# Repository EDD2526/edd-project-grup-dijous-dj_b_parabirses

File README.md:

# Projecte DJ_B_PARABRISAS

>**Autors:Héctor Rodriguez y MariPaz Carreño
>**Versió: VFinal

----------

## Objectiu

>Crear un pcb para un limpia parabrisas, la cual tendrá control a través de un microcontrolador.
EL objetivo principal es  mantener  la luna del cristal limpia, para ello tenemos un sensor de lluvia que detectará la lluvia, un calefactor para que no se empañe, y bombas de agua que permitan en todo momento limpiar la luna.

## Diagrama de blocs

### Descripció/funcionalitat de cada bloc

  Tenemos el micro en el centro que funcionará como cerebro de todo.
  Como se puede observar uno de los sería la alimentación, consta de un conector que permite meter 12V, después pasa por un convertidor        
  DC-DC, para obtener 5V y por último un regulador para tener un voltaje de 3V.
  Por otro lado tenemos el bloque de potencia: consta de los drivers y motores de los limpiaparabrisas, de los circuitos relé tanto para 
  las bombas, como para el calefactor, y de finales de carrera que permitan volver a su estado inicial.   
  Por último un bloque de conexión/usuario: consta del BUS CAN, este permite la comunicación con otros módulos, el UART, transforma los 
  datos de forma que puedan ser leídos/enviados a un ordenador. También esta el sensor digital de lluvia que detecta cuando hay lluvia y 
  que el motor se ponga en marcha, y por último tendríamos la botonera: sirve para que el usuario acomode el modo del limpiaparabrisas o 
  encienda y apague el calefactor.       
  
-----------

## Requisits / Especificacions

* Alimentació: 12V d’entrada, regulada a 5V i 3.3V
* Microcontrolador: PIC24HJ64GP504
* Regulador buck: LM2596S-5 per obtenir 5V
* Regulador LDO: LM1117DT-3.3 per obtenir 3.3V
* Protecció d’entrada: díode TVS SM6T24A
* Díodes de protecció: D4, D5 i D6 per protegir contra pics inductius
* Comunicació CAN: transceptor TJA1049TK-3
* Comunicació RS232: MAX232
* Oscil·lador: cristall Y1 
* Condensadors de desacoblament: 100nF i 1uF
* Condensadors de filtratge: 680uF, 220uF, 100uF i 10uF
* Resistències: valors diversos per polarització, pull-up, pull-down i limitació de corrent
* Punts de test: TP1, TP2 i TP3

-----------

## Components

| Descripció | Ref | Package | Datasheet | Proveïdor | Preu | Unitats |
|---|---|---|---|---|---|---|
| Capacitor 100nF | C1,C2,C10,C16 | 0805 | ~ | Mouser | — | 4 |
| Capacitor 20pF | C3,C4 | 0805 | ~ | Mouser | — | 2 |
| Capacitor 1uF | C5,C6,C7,C8,C9 | 0805 | ~ | Mouser | — | 5 |
| Capacitor 680uF | C11 | 0805 | ~ | Mouser | — | 1 |
| Capacitor 220uF | C12 | 0805 | ~ | Mouser | — | 1 |
| Capacitor 10uF | C13,C14 | CP Radial D5.0mm P2.50mm | — | Mouser | — | 2 |
| Capacitor 100uF | C15 | CP Radial D5.0mm P2.50mm | — | Mouser | — | 1 |
| Capacitor 10pF | C17 | 0805 | ~ | Mouser | — | 1 |
| Capacitor 100pF | C19 | 0805 | ~ | Mouser | — | 1 |
| LED | D2 | LED 0805 | ~ | Mouser | — | 1 |
| Diodo TVS SM6T24A | D3 | SMB | https://www.st.com/resource/en/datasheet/sm6t.pdf | Mouser | — | 1 |
| Diodo genérico | D4,D5,D6 | 0201 | ~ | Mouser | — | 3 |
| Ferrita | FB1 | LairdTech 28C0236-0JW-10 | ~ | Mouser | — | 1 |
| Final de carrera SPDT | FINALCARRERA1,FINALCARRERA2 | XKB DM1-16UC-1 | ~ | Mouser | — | 2 |
| Conector 1x05 | J1 | PinHeader 1x05 2.54mm | ~ | Mouser | — | 1 |
| Conector DE9 | J2,J3 | DSUB-9 Horizontal | ~ | Mouser | — | 2 |
| Conector 1x02 | J4 | PinHeader 1x02 2.54mm | ~ | Mouser | — | 1 |
| Jumper 3 pines | JP1 | PinHeader 1x03 2.54mm | ~ | Mouser | — | 1 |
| Relé SPST-NO Fujitsu FTR-LYAA005x | K2,K3,K4 | Relay THT Vertical | https://www.fujitsu.com/sg/imagesgig5/ftr-ly.pdf | Mouser | — | 3 |
| Inductor 33uH | L1 | 0603 | ~ | Mouser | — | 1 |
| Motor DC / Bornera salida | M1,M2,M3,M5 | TerminalBlock 2P P5.00mm | ~ | Mouser | — | 4 |
| Transistor NPN MMBT3904 | Q2,Q3,Q4 | SOT-23 | https://www.onsemi.com/pdf/datasheet/pzt3904-d.pdf | Mouser | — | 3 |
| Resistencia 1k | R2,R3,R7,R8 | 0603 | ~ | Mouser | — | 4 |
| Resistencia 4.7k | R4,R13,R14 | 0603 | ~ | Mouser | — | 3 |
| Resistencia 121Ω | R5 | 0603 | ~ | Mouser | — | 1 |
| Resistencia 200Ω | R6 | 0603 | ~ | Mouser | — | 1 |
| Resistencia 10k | R9 | 0603 | ~ | Mouser | — | 1 |
| Resistencia 4.7k | R10 | 0603 | ~ | Mouser | — | 1 |
| Resistencia calefactor | R11 | 2512 | ~ | Mouser | — | 1 |
| Resistencia 60Ω | R12,R17 | 0201 | ~ | Mouser | — | 2 |
| Resistencia 10k | R15,R16 | 0603 | ~ | Mouser | — | 2 |
| Resistencia 7.6k | R18,R22,R23 | 0603 | ~ | Mouser | — | 3 |
| Resistencia 10k | R19,R20,R21 | 0201 | ~ | Mouser | — | 3 |
| Pulsador calefactor | SW1 | Alps SKRK SMD | ~ | Mouser | — | 1 |
| Pulsador bombas | SW2 | Alps SKRK SMD | ~ | Mouser | — | 1 |
| Pulsador | SW3 | Alps SKRK SMD | ~ | Mouser | — | 1 |
| Selector rotativo SP3T | SW5 | NKK NR01 THT | https://www.nkkswitches.com/pdf/NR01%20Rotaries.pdf | Mouser | — | 1 |
| Test point | TP1,TP2,TP3 | Keystone 5015 Micro Mini | ~ | Mouser | — | 3 |
| Regulador LDO 3.3V LM1117DT-3.3 | U1 | TO-252-3 | http://www.ti.com/lit/ds/symlink/lm1117.pdf | Mouser | — | 1 |
| Regulador buck 5V LM2596S-5 | U2 | TO-263-5 | http://www.ti.com/lit/ds/symlink/lm2596.pdf | Mouser | — | 1 |
| Driver motor DRV8871DDA | U3,U7 | HTSOP-8 PowerPAD | http://www.ti.com/lit/ds/symlink/drv8871.pdf | Mouser | — | 2 |
| Microcontrolador PIC24HJ64GP504 | U4 | QFN-44 7x7mm | — | Mouser | — | 1 |
| Sensor humedad/temperatura HDC2080 | U6 | Texas S-PWSON-N6 | http://www.ti.com/lit/ds/symlink/hdc2080.pdf | Mouser | — | 1 |
| Transceptor CAN TJA1049TK-3 | U8 | HVSON-8 | https://www.nxp.com/docs/en/data-sheet/TJA1049.pdf | Mouser | — | 1 |
| Transceptor RS232 MAX232 | U9 | SOIC-16 | http://www.ti.com/lit/ds/symlink/max232.pdf | Mouser | — | 1 |
| Cristal | Y1 | SMD EuroQuartz EQ161 2Pin | ~ | Mouser | — | 1 |

-----------

## Software

### Eines:

  * KiCad 9.0 o superior
  * 

### Configuraci&#243; :

  * 

### Funcionalitats:

  Gestionar el movimiento de las escobillas, el rociado del líquido limpiador mediante dos bombas y el calentamiento del sistema mediante un calefactor.
Cuando el usuario activa el mando, la PCB recibe la señal y enciende el motor del limpiaparabrisas en el modo seleccionado. También puede activar una de las dos bombas, por ejemplo una para el parabrisas delantero y otra para el cristal trasero, enviando líquido limpiador antes o durante el movimiento de las escobillas.
Además, la PCB controla el calefactor, que sirve para calentar el líquido o la zona del sistema de lavado, evitando congelación y mejorando el funcionamiento en bajas temperaturas.

-----------

## Historial de canvis

| Data | Autor     | Branch | Versi&#243; | Descripci&#243; |
| --- | --- | --- | --- | --- |
|  28/03/2023 | mlopez | Master | initial commit | Primera versi&#243; d'esquem&#224;tic i selecci&#243; de components |

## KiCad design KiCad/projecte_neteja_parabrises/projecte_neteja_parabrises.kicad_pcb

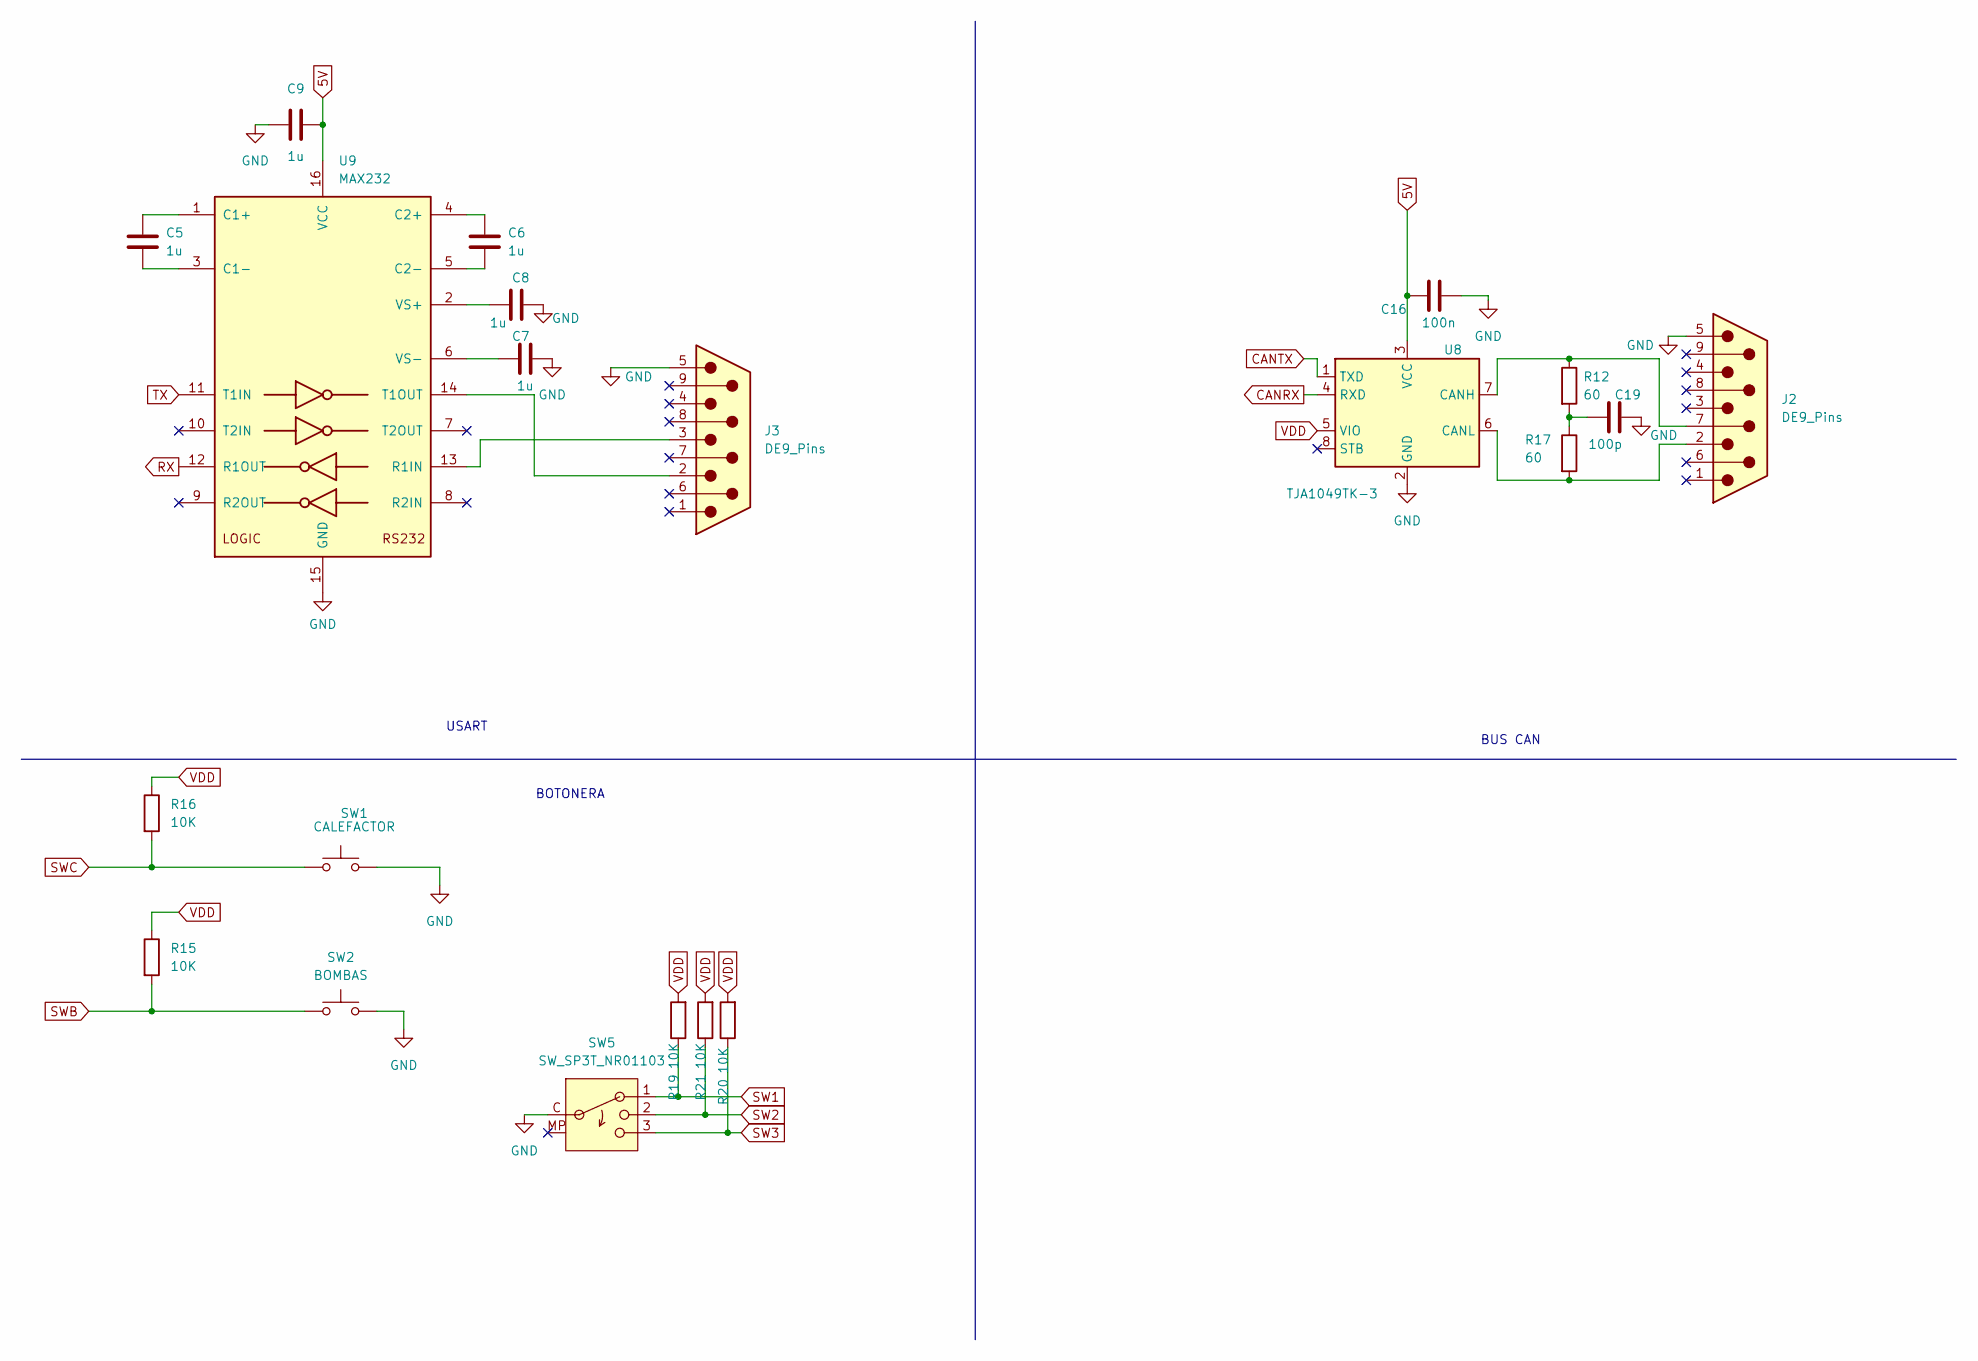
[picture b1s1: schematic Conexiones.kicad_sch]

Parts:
C5, C6, C7, C8, C9: 1u; C_0805_2012Metric
C16: 100n; C_0805_2012Metric
C19: 100p; C_0805_2012Metric
J2, J3: DE9_Pins; DSUB-9_Pins_Horizontal_P2.77x2.84mm_EdgePinOffset9.40mm
R12, R17: 60; R_0201_0603Metric_Pad0.64x0.40mm_HandSolder
R15, R16: 10K; R_0603_1608Metric_Pad0.98x0.95mm_HandSolder
R19, R20, R21: 10K; R_0201_0603Metric_Pad0.64x0.40mm_HandSolder
SW1: CALEFACTOR; SW_Push_SPST_NO_Alps_SKRK
SW2: BOMBAS; SW_Push_SPST_NO_Alps_SKRK
SW5: SW_SP3T_NR01103; SW_NKK_NR01
U8: TJA1049TK-3; HVSON-8-1EP_3x3mm_P0.65mm_EP1.6x2.4mm
U9: MAX232; JEITA_SOIC-16_3.9x9.9mm_P1.27mm

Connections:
5V: C9.2, C16.1, U8.3 (VCC), U9.16 (VCC); also elsewhere on the board
CANRX: U8.4 (RXD); also elsewhere on the board
CANTX: U8.1 (TXD); also elsewhere on the board
GND: C7.1, C8.1, C9.1, C16.2, C19.2, J2.5, J3.5, SW1.2, SW2.2, SW5.C (Common), U8.2 (GND), U8.9 (GND), U9.15 (GND); also elsewhere on the board
unnamed: C19.1, R12.2, R17.1
unnamed: J2.7, R12.1, U8.7 (CANH)
unnamed: J2.2, R17.2, U8.6 (CANL)
unnamed: C5.1, U9.1 (C1+)
unnamed: C5.2, U9.3 (C1-)
unnamed: C6.1, U9.4 (C2+)
unnamed: C6.2, U9.5 (C2-)
unnamed: J3.3, U9.13 (R1IN)
unnamed: J3.2, U9.14 (T1OUT)
unnamed: C8.2, U9.2 (VS+)
unnamed: C7.2, U9.6 (VS-)
RX: U9.12 (R1OUT); also elsewhere on the board
SW1: R19.1, SW5.1; also elsewhere on the board
SW2: R21.1, SW5.2; also elsewhere on the board
SW3: R20.1, SW5.3; also elsewhere on the board
SWB: R15.2, SW2.1; also elsewhere on the board
SWC: R16.2, SW1.1; also elsewhere on the board
TX: U9.11 (T1IN); also elsewhere on the board
VDD: R15.1, R16.1, R19.2, R20.2, R21.2, U8.5 (VIO); also elsewhere on the board

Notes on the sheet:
BUS CAN
USART
BOTONERA

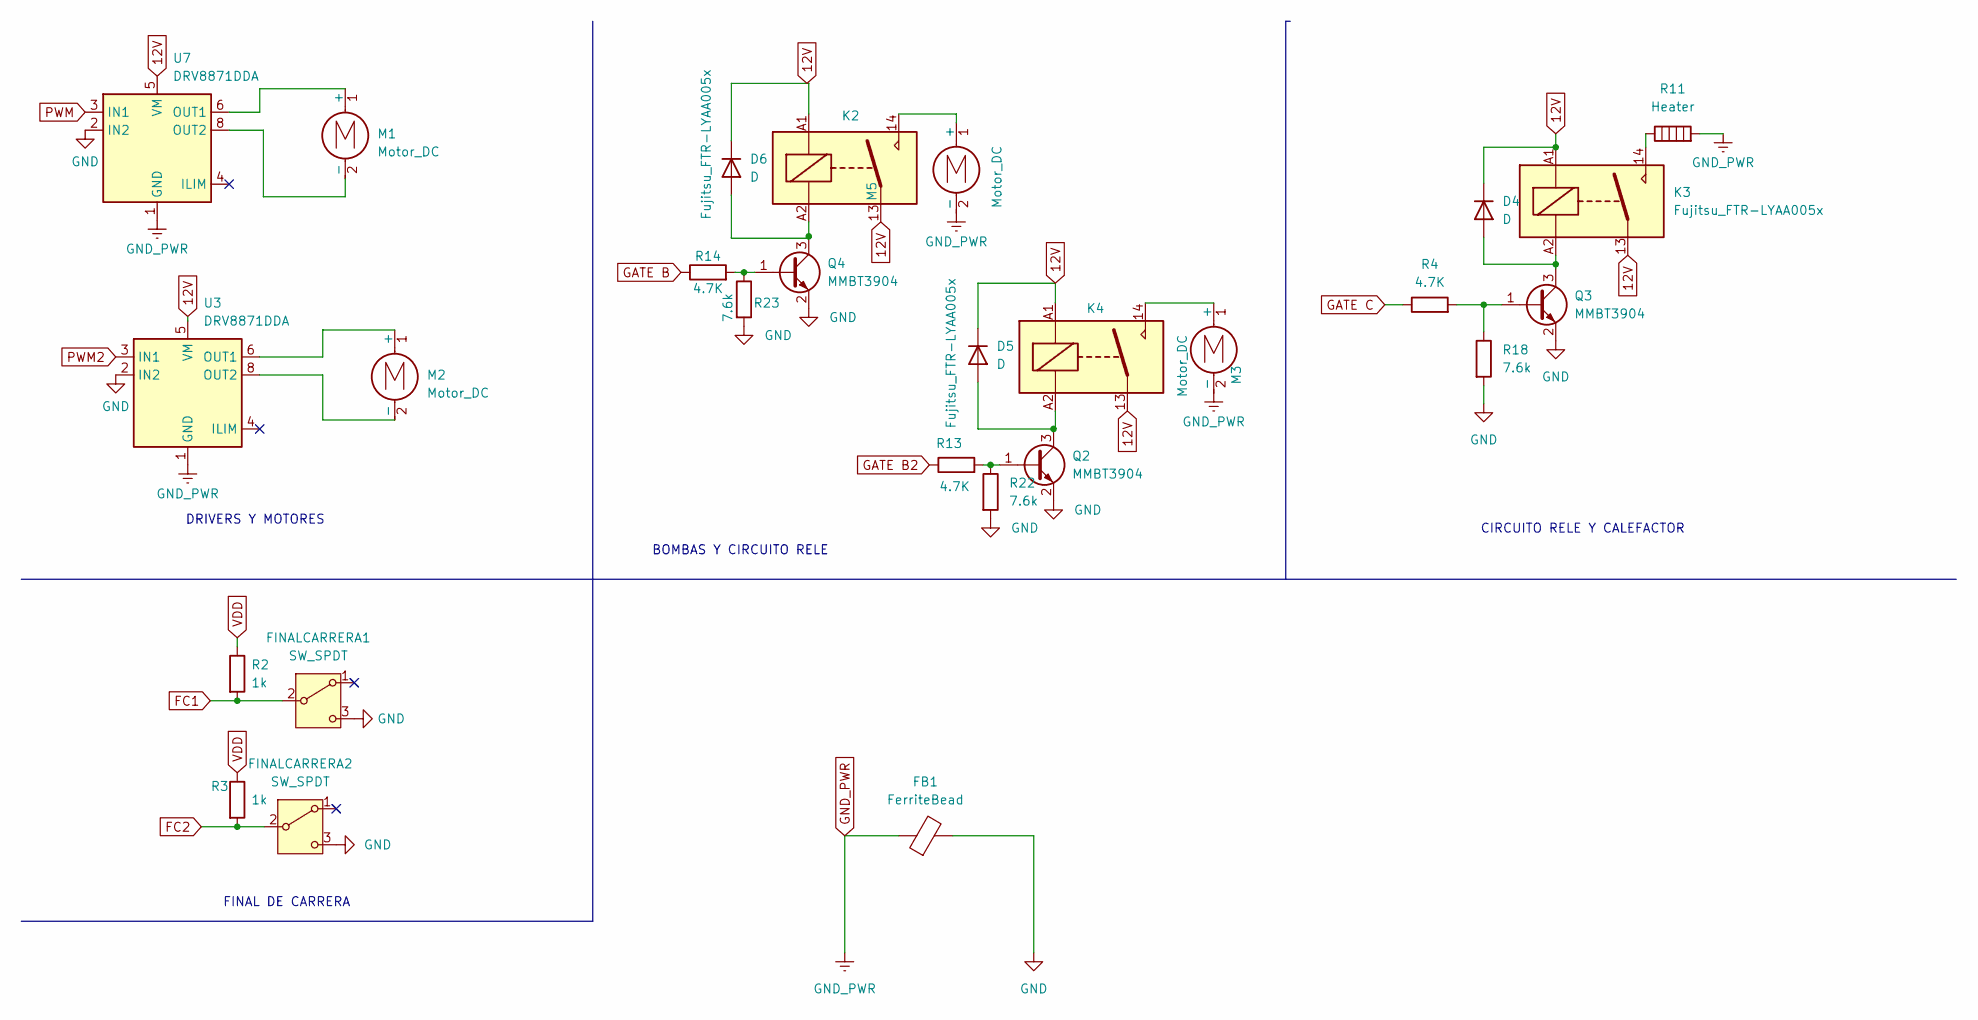
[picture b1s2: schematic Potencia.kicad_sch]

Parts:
D4, D5, D6: D; D_0201_0603Metric_Pad0.64x0.40mm_HandSolder
FB1: FerriteBead; LairdTech_28C0236-0JW-10
FINALCARRERA1, FINALCARRERA2: SW_SPDT; SW_XKB_DM1-16UC-1
K2, K3, K4: Fujitsu_FTR-LYAA005x; Relay_SPST-NO_Fujitsu_FTR-LYAA005x_FormA_Vertical
M1, M2, M3, M5: Motor_DC; TerminalBlock_MaiXu_MX126-5.0-02P_1x02_P5.00mm
Q2, Q3, Q4: MMBT3904; SOT-23
R2, R3: 1k; R_0603_1608Metric_Pad0.98x0.95mm_HandSolder
R4, R13, R14: 4.7K; R_0603_1608Metric_Pad0.98x0.95mm_HandSolder
R11: Heater; R_2512_6332Metric_Pad1.40x3.35mm_HandSolder
R18, R22, R23: 7.6k; R_0603_1608Metric_Pad0.98x0.95mm_HandSolder
U3, U7: DRV8871DDA; Texas_HTSOP-8-1EP_3.9x4.9mm_P1.27mm_EP2.95x4.9mm_Mask2.4x3.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

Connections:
12V: D4.1 (K), D5.1 (K), D6.1 (K), K2.13, K2.A1, K3.13, K3.A1, K4.13, K4.A1, U3.5 (VM), U7.5 (VM); also elsewhere on the board
FC1: FINALCARRERA1.2 (B), R2.2; also elsewhere on the board
FC2: FINALCARRERA2.2 (B), R3.2; also elsewhere on the board
GATE B: R14.1; also elsewhere on the board
GATE B2: R13.1; also elsewhere on the board
GATE C: R4.1; also elsewhere on the board
GND: FB1.2, FINALCARRERA1.3 (C), FINALCARRERA2.3 (C), Q2.2 (E), Q3.2 (E), Q4.2 (E), R18.2, R22.2, R23.2, U3.2 (IN2), U7.2 (IN2); also elsewhere on the board
GND_PWR: FB1.1, M3.2 (-), M5.2 (-), R11.2, U3.1 (GND), U3.7 (GND), U3.9 (GND), U7.1 (GND), U7.7 (GND), U7.9 (GND)
unnamed: D4.2 (A), K3.A2, Q3.3 (C)
unnamed: D5.2 (A), K4.A2, Q2.3 (C)
unnamed: D6.2 (A), K2.A2, Q4.3 (C)
unnamed: K3.14, R11.1
unnamed: M1.1 (+), U7.6 (OUT1)
unnamed: M1.2 (-), U7.8 (OUT2)
unnamed: M2.1 (+), U3.6 (OUT1)
unnamed: M2.2 (-), U3.8 (OUT2)
unnamed: K4.14, M3.1 (+)
unnamed: K2.14, M5.1 (+)
unnamed: Q2.1 (B), R13.2, R22.1
unnamed: Q3.1 (B), R4.2, R18.1
unnamed: Q4.1 (B), R14.2, R23.1
PWM: U7.3 (IN1); also elsewhere on the board
PWM2: U3.3 (IN1); also elsewhere on the board
VDD: R2.1, R3.1; also elsewhere on the board

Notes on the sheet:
FINAL DE CARRERA
DRIVERS Y MOTORES
BOMBAS Y CIRCUITO RELE
CIRCUITO RELE Y CALEFACTOR

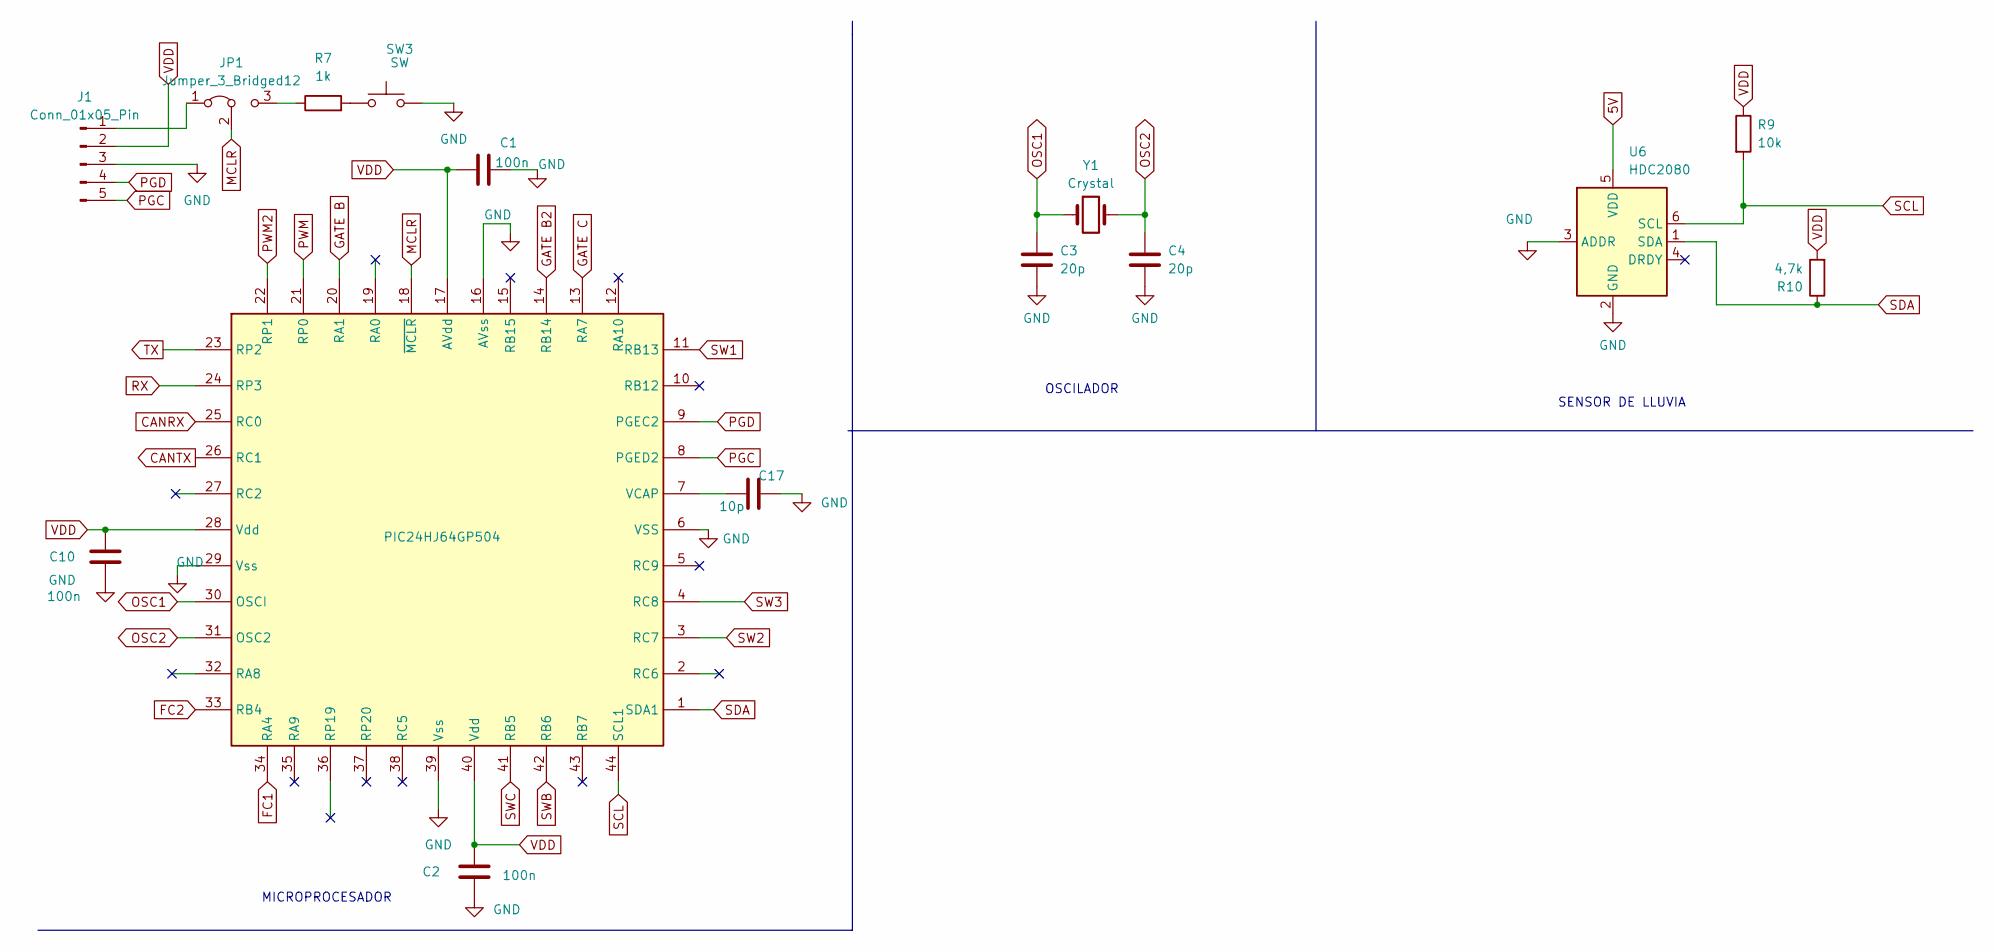
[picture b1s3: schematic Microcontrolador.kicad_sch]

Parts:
C1, C2, C10: 100n; C_0805_2012Metric
C3, C4: 20p; C_0805_2012Metric
C17: 10p; C_0805_2012Metric
J1: Conn_01x05_Pin; PinHeader_1x05_P2.54mm_Vertical
JP1: Jumper_3_Bridged12; PinHeader_1x03_P2.54mm_Vertical
R7: 1k; R_0603_1608Metric_Pad0.98x0.95mm_HandSolder
R9: 10k; R_0603_1608Metric_Pad0.98x0.95mm_HandSolder
R10: 4,7k; R_0603_1608Metric_Pad0.98x0.95mm_HandSolder
SW3: SW; SW_Push_SPST_NO_Alps_SKRK
U4: PIC24HJ64GP504; QFN-44-1EP_7x7mm_P0.5mm_EP5.2x5.2mm
U6: HDC2080; Texas_S-PWSON-N6-HDC2080
Y1: Crystal; Crystal_SMD_EuroQuartz_EQ161-2Pin_3.2x1.5mm_HandSoldering

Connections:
5V: U6.5 (VDD); also elsewhere on the board
CANRX: U4.25 (RC0); also elsewhere on the board
CANTX: U4.26 (RC1); also elsewhere on the board
FC1: U4.34 (RA4); also elsewhere on the board
FC2: U4.33 (RB4); also elsewhere on the board
GATE B: U4.20 (RA1); also elsewhere on the board
GATE B2: U4.14 (RB14); also elsewhere on the board
GATE C: U4.13 (RA7); also elsewhere on the board
GND: C1.1, C2.1, C3.2, C4.2, C10.1, C17.2, J1.3, SW3.2, U4.6 (VSS), U4.16 (AVss), U4.29 (Vss), U4.39 (Vss), U6.2 (GND), U6.3 (ADDR); also elsewhere on the board
MCLR: JP1.2 (C), U4.18 (~MCLR)
unnamed: J1.1, JP1.1 (A)
unnamed: JP1.3 (B), R7.1
unnamed: R7.2, SW3.1
unnamed: C17.1, U4.7 (VCAP)
OSC1: C3.1, U4.30 (OSCI), Y1.1
OSC2: C4.1, U4.31 (OSC2), Y1.2
PGC: J1.5, U4.8 (PGED2)
PGD: J1.4, U4.9 (PGEC2)
PWM: U4.21 (RP0); also elsewhere on the board
PWM2: U4.22 (RP1); also elsewhere on the board
RX: U4.24 (RP3); also elsewhere on the board
SCL: R9.2, U4.44 (SCL1), U6.6 (SCL)
SDA: R10.1, U4.1 (SDA1), U6.1 (SDA)
SW1: U4.11 (RB13); also elsewhere on the board
SW2: U4.3 (RC7); also elsewhere on the board
SW3: U4.4 (RC8); also elsewhere on the board
SWB: U4.42 (RB6); also elsewhere on the board
SWC: U4.41 (RB5); also elsewhere on the board
TX: U4.23 (RP2); also elsewhere on the board
VDD: C1.2, C2.2, C10.2, J1.2, R9.1, R10.2, U4.17 (AVdd), U4.28 (Vdd), U4.40 (Vdd); also elsewhere on the board

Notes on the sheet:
SENSOR DE LLUVIA
OSCILADOR
MICROPROCESADOR

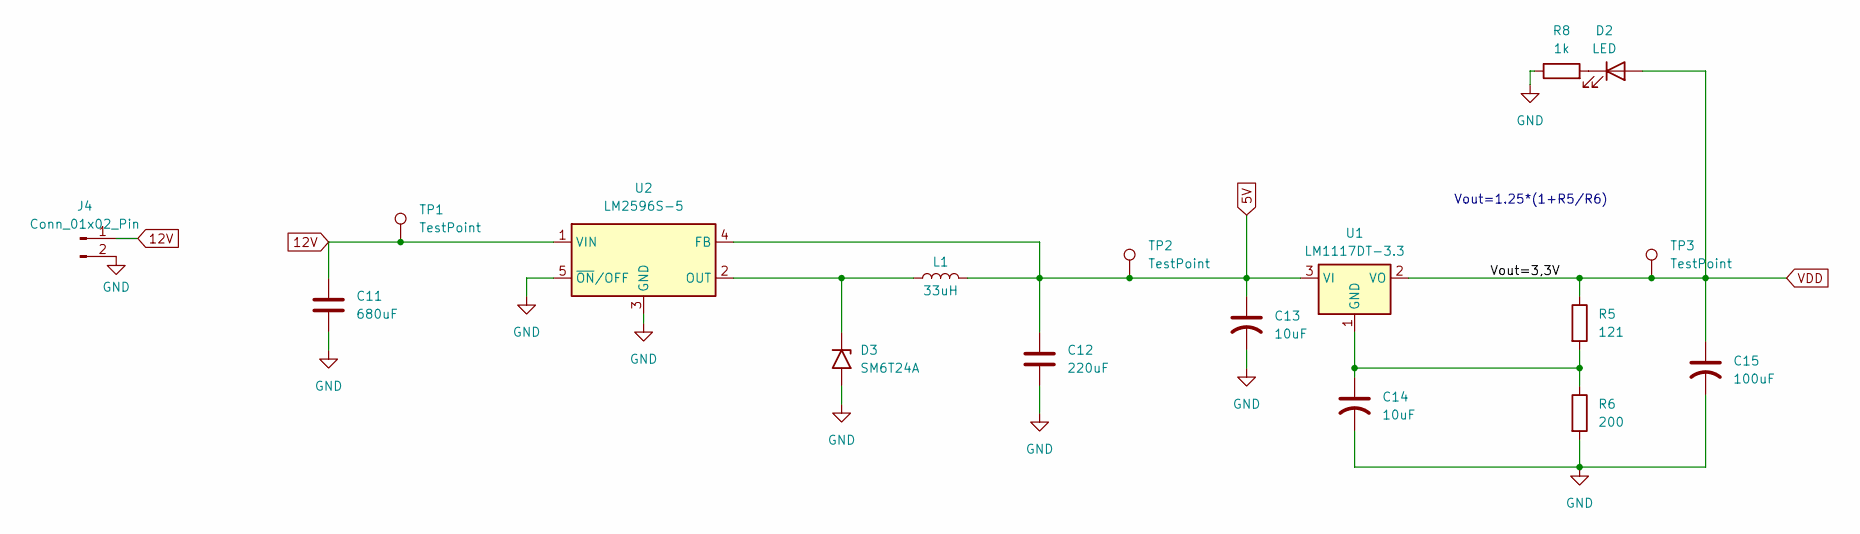
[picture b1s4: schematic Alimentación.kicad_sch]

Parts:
C11: 680uF; C_0805_2012Metric
C12: 220uF; C_0805_2012Metric
C13, C14: 10uF; CP_Radial_D5.0mm_P2.50mm
C15: 100uF; CP_Radial_D5.0mm_P2.50mm
D2: LED; LED_0805_2012Metric_Pad1.15x1.40mm_HandSolder
D3: SM6T24A; D_SMB
J4: Conn_01x02_Pin; PinHeader_1x02_P2.54mm_Vertical
L1: 33uH; L_0603_1608Metric_Pad1.05x0.95mm_HandSolder
R5: 121; R_0603_1608Metric_Pad0.98x0.95mm_HandSolder
R6: 200; R_0603_1608Metric_Pad0.98x0.95mm_HandSolder
R8: 1k; R_0603_1608Metric_Pad0.98x0.95mm_HandSolder
TP1, TP2, TP3: TestPoint; TestPoint_Keystone_5015_Micro_Mini
U1: LM1117DT-3.3; TO-252-3_TabPin2
U2: LM2596S-5; TO-263-5_TabPin3

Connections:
5V: C12.1, C13.1, L1.2, TP2.1, U1.3 (VI), U2.4 (FB); also elsewhere on the board
12V: C11.1, J4.1, TP1.1, U2.1 (VIN); also elsewhere on the board
GND: C11.2, C12.2, C13.2, C14.2, C15.2, D3.2 (A2), J4.2, R6.2, R8.1, U2.3 (GND), U2.5 (~ON/OFF); also elsewhere on the board
unnamed: D2.1 (K), R8.2
unnamed: D3.1 (A1), L1.1, U2.2 (OUT)
unnamed: C14.1, R5.2, R6.1, U1.1 (GND)
VDD: C15.1, D2.2 (A), R5.1, TP3.1, U1.2 (VO); also elsewhere on the board

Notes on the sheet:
Vout=1.25*(1+R5/R6)

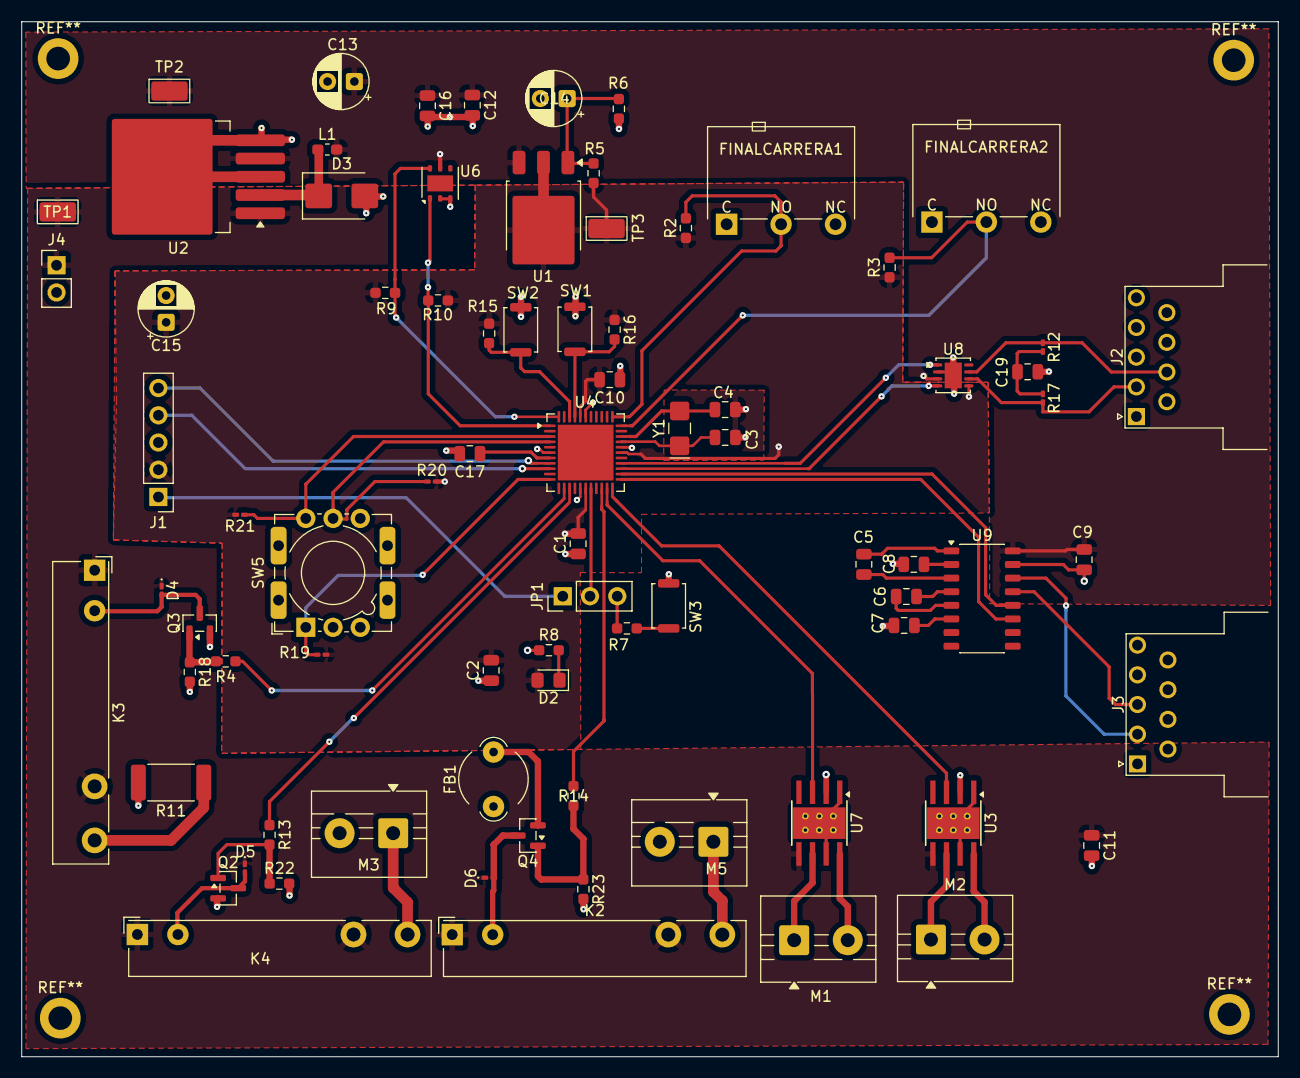
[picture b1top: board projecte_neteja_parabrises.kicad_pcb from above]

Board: 2 copper layers, 117.2 x 96.5 mm, 80 parts (0 on the bottom side), 59 nets.

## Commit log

2026-03-12 modficacion readme
2026-03-12 esquematico version 1
2026-03-16 projecte kicad
2026-03-16 Backlink to CADLAB.io has been added.
2026-03-18 esquematico
2026-03-18 prova
2026-03-18 Prueba Potencia
2026-03-18 data-sheet
2026-03-18 Potencia actualizada
2026-03-18 alimentacion
2026-03-18 error raro
2026-03-18 micro
2026-03-18 botonera
2026-03-18 BOMBAS Y FINAL DEL CARRERA
2026-03-18 POTENCIA ACABADA
2026-03-18 V1 SCH
2026-03-19 SCH V1
2026-03-19 SCH ALIMETNACION
2026-03-19 README
2026-03-19 alimentacio millora
2026-03-19 alimentacio acabada
2026-03-19 UART ACABADO
2026-03-19 alimentacio arreglada
2026-03-19 MICRO ACTUALIZADA
2026-03-19 Readme avanç
2026-03-20 ESQUEMATICO V2
2026-03-24 Error de nombres solucionado
2026-03-24 huellas
2026-03-25 millora alimentacio
2026-03-25 Actualización huellas
2026-03-25 huella bateria
2026-03-25 huella c electrolitica
2026-03-25 formula
2026-03-25 MCLR
2026-03-25 arreglos
2026-03-26 Placa definitiva
2026-03-26 readme foto
2026-03-26 millora botonera
2026-03-26 Actualizacion errores
2026-03-26 detector lluvia
2026-03-26 potencia cambios
2026-04-01 POTENCIA GND
2026-04-01 huella ferrita
2026-04-06 actualizacion componentes placa
2026-04-07 Pines
2026-04-08 huella
2026-04-09 placements restantes
2026-04-09 pcb placement
2026-04-16 test points
2026-04-16 actualitzacio pcb
2026-04-17 pcb cristal
2026-04-22 vias pcb
2026-04-30 pdf presentacio
